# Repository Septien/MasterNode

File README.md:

A node that contains a LoRa transciever and a WiFi module, for sending data to the cloud (Cloudino).

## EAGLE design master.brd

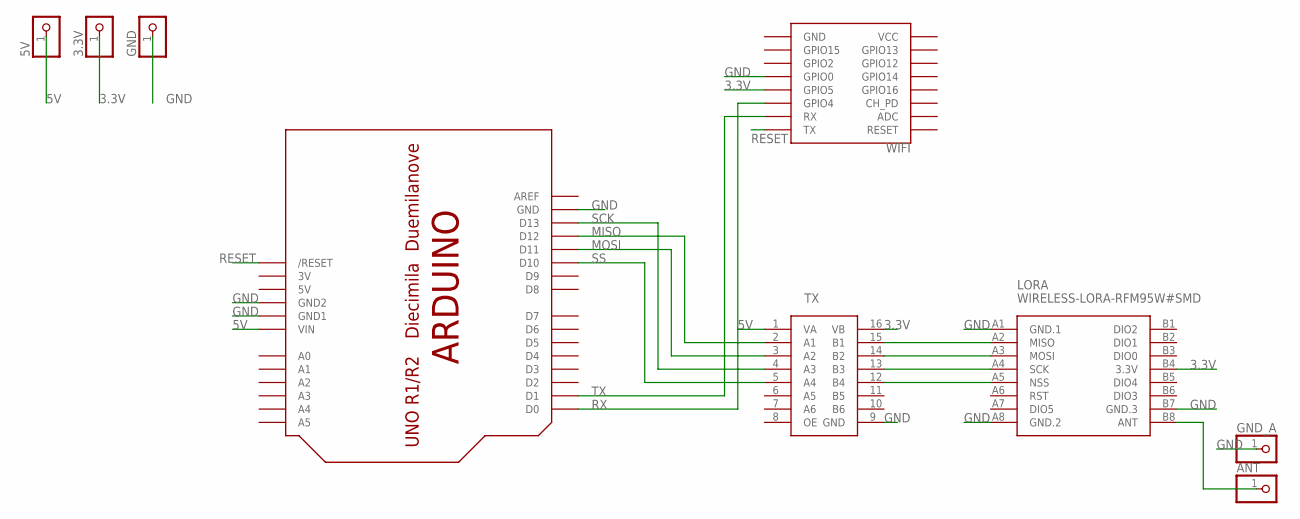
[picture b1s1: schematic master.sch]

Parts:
3.3V, 5V: PINHD-1X1; 1X01
ANT: PINHD-1X1; 1X01
GND: PINHD-1X1; 1X01
GND_A: PINHD-1X1; 1X01
LORA: WIRELESS-LORA-RFM95W#SMD
TX: TX50108E
U$1: ARDUINOUNO; ARDUINO
WIFI: ESP12

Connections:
3.3V: 3.3V.1, LORA.B4 (3.3V), TX.16 (VB), WIFI.GPIO5
3V: U$1.3V
5V: 5V.1, TX.1 (VA), U$1.5V, U$1.VIN
GND: GND.1, GND_A.1, LORA.A1 (GND.1), LORA.A8 (GND.2), LORA.B7 (GND.3), TX.9 (GND), U$1.GND, U$1.GND1, U$1.GND2, WIFI.GPIO0
MISO: TX.2 (A1), U$1.D12
MOSI: TX.3 (A2), U$1.D11
unnamed: ANT.1, LORA.B8 (ANT)
unnamed: LORA.A2 (MISO), TX.15 (B1)
unnamed: LORA.A3 (MOSI), TX.14 (B2)
unnamed: LORA.A4 (SCK), TX.13 (B3)
unnamed: LORA.A5 (NSS), TX.12 (B4)
RESET: U$1.RESET (/RESET), WIFI.TX
RX: U$1.D0, WIFI.GPIO4
SCK: TX.4 (A3), U$1.D13
SS: TX.5 (A4), U$1.D10
TX: U$1.D1, WIFI.RX

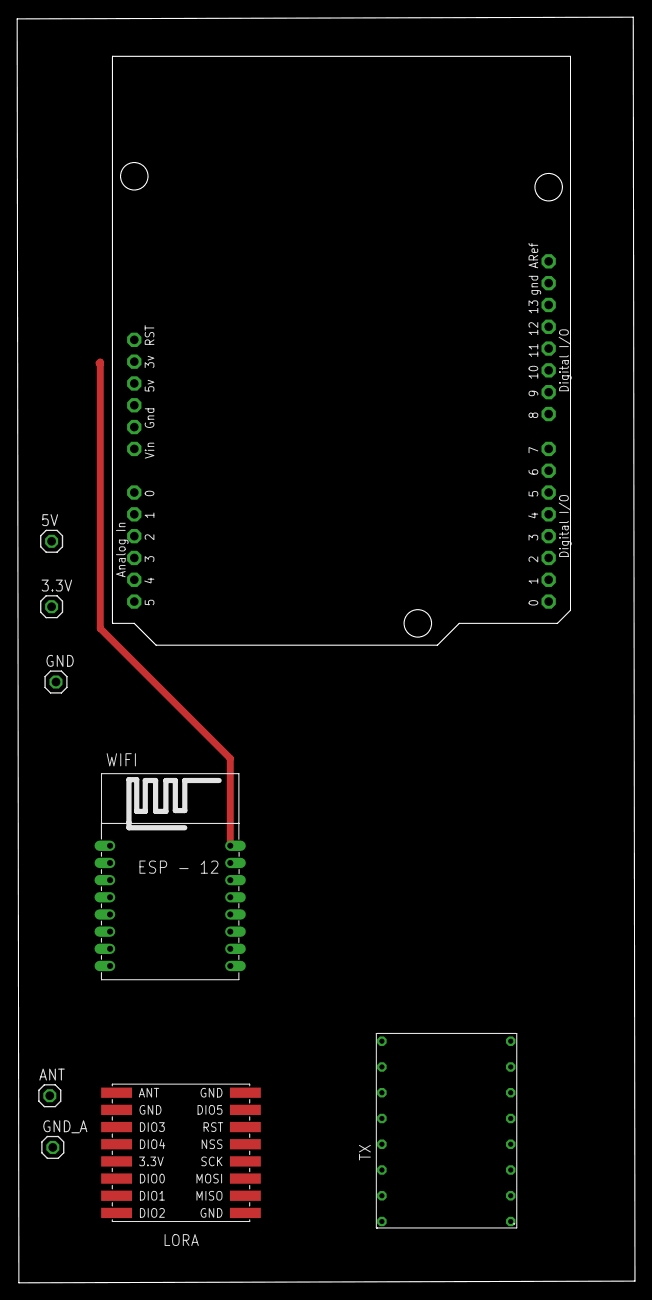
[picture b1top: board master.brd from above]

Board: 2 copper layers, 72.0 x 147.4 mm, 9 parts (0 on the bottom side), 15 nets.

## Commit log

2020-05-13 First commit.
2020-05-13 Add master node project.

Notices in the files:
parts and their libraries:
dht22: Released under the Creative Commons Attribution 4.0 International License: http://creativecommons.org/licenses/by/4.0
